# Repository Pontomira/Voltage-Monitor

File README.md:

# Voltage-Monitor
I'm trying to build a voltage monitor for Li-Po batteries, in my case 6s and i used texas instruments devices to make the gauge meter, charging and discharging control

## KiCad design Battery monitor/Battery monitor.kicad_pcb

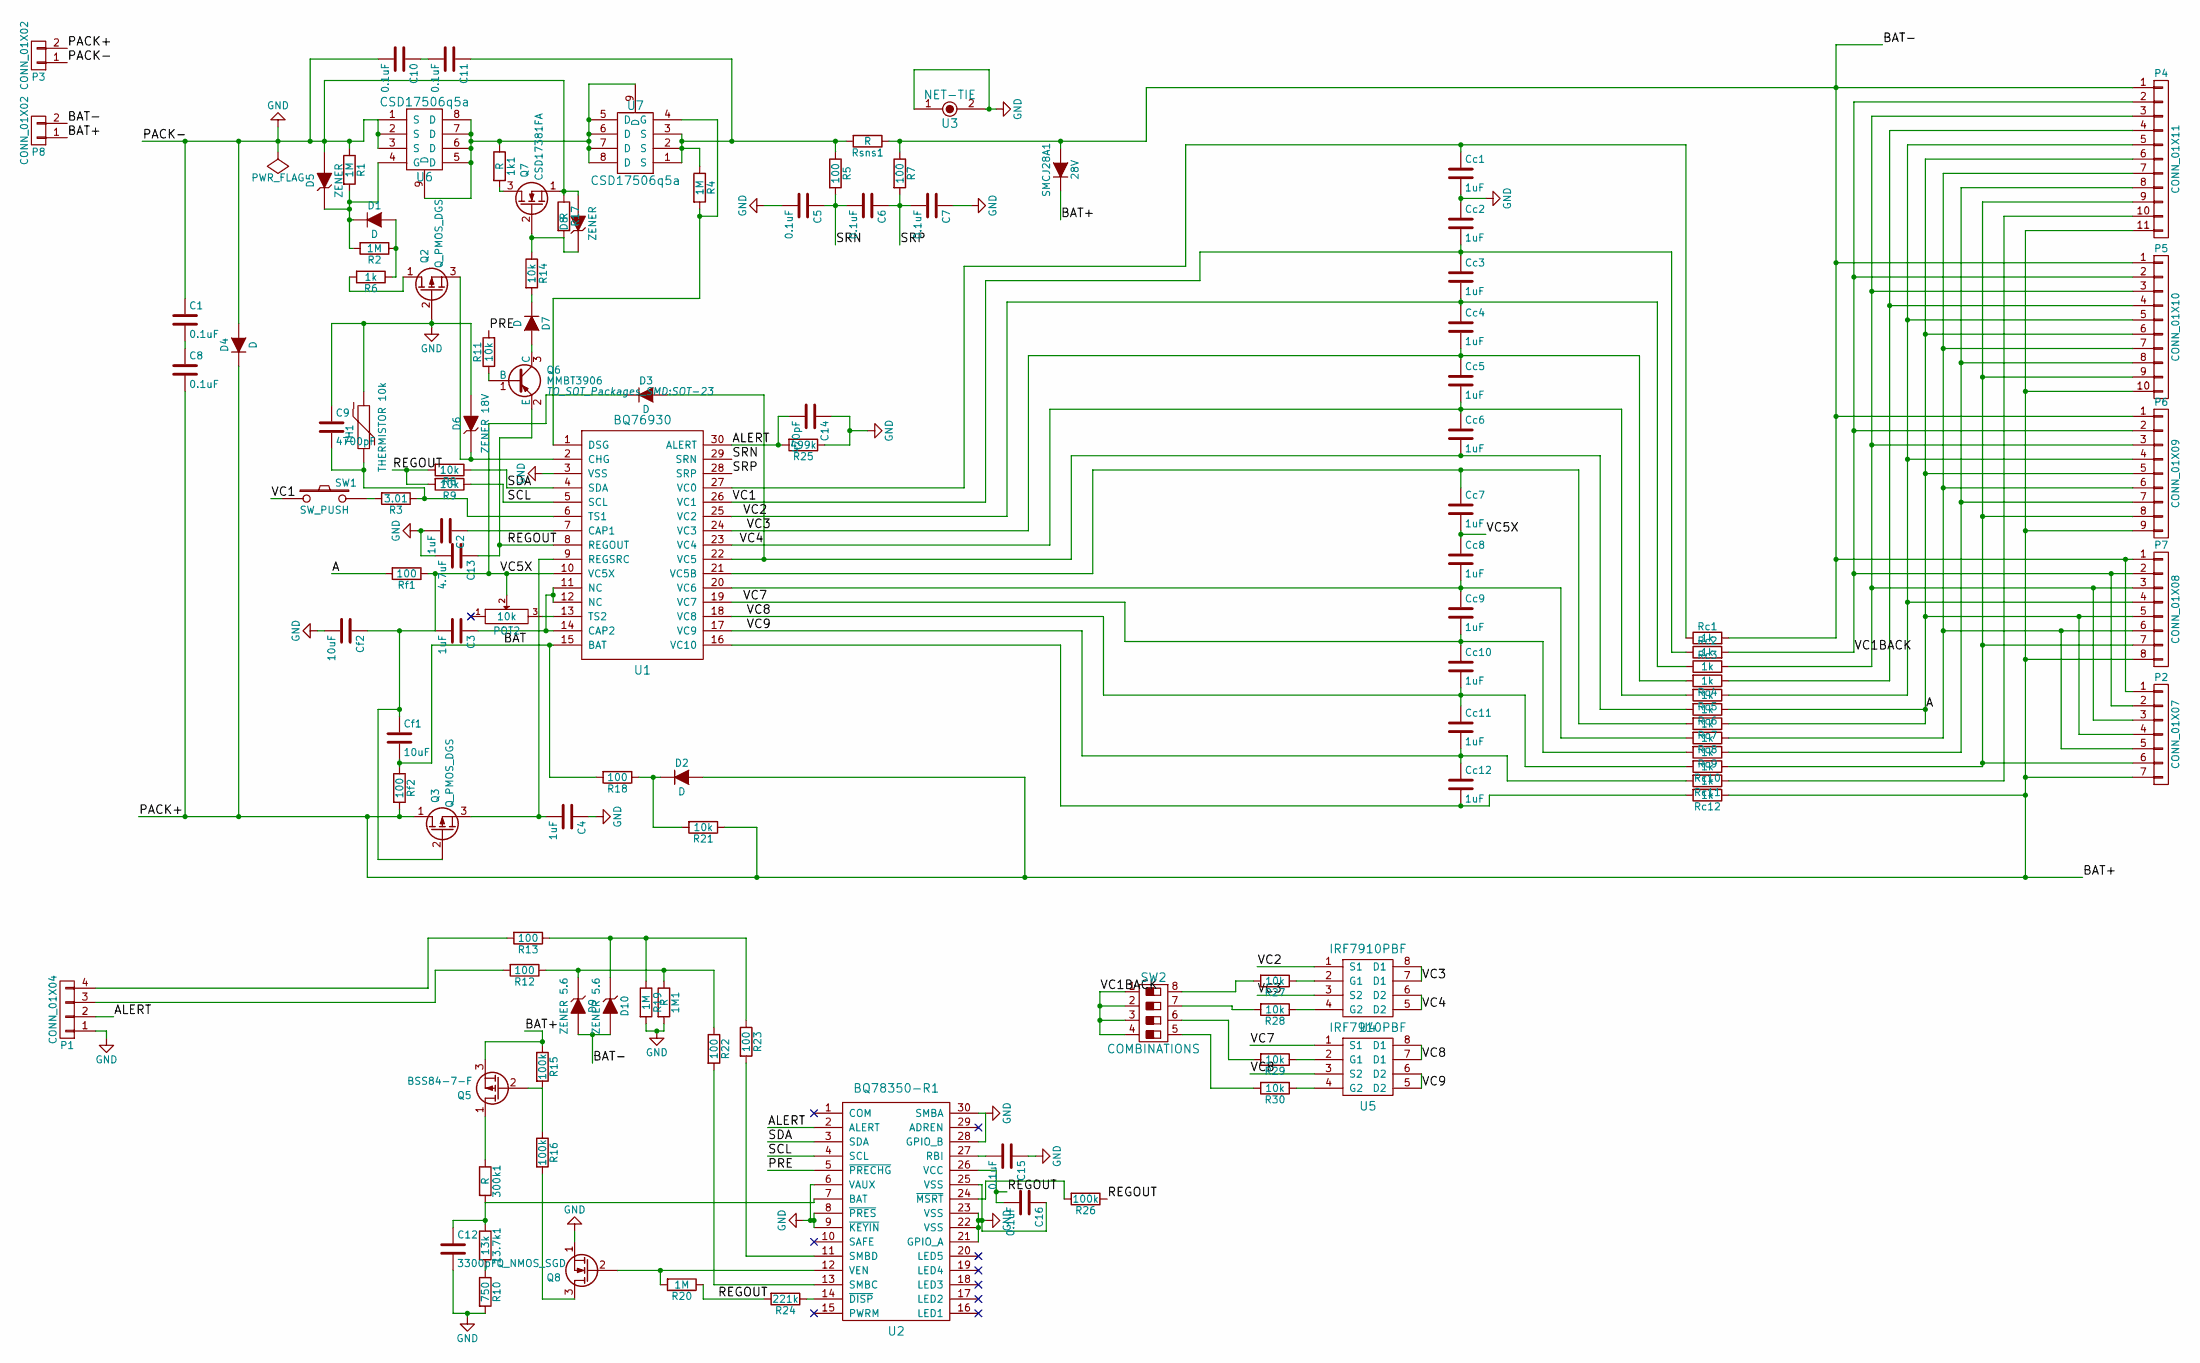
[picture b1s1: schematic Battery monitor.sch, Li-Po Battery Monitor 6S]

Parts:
1M1, 1k1, 300k1: R; R_1206_HandSoldering
13.7k1: 13k; R_1206_HandSoldering
C1: 0.1uF; R_0805_HandSoldering
C2, C3, C4: 1uF; C_0402
C5, C6, C7, C8, C10, C11, C15, C16: 0.1uF; C_0805_HandSoldering
C9: 4700pF; C_0805_HandSoldering
C12: 3300pF; C_0603_HandSoldering
C13: 4.7uF; C_0805_HandSoldering
C14: 470pF; C_0805_HandSoldering
Cc1, Cc2, Cc3, Cc4, Cc5, Cc6, Cc7, Cc8, Cc9, Cc10, Cc11, Cc12: 1uF; C_0402
Cf1, Cf2: 10uF; C_1206_HandSoldering
D1, D2, D3, D4, D7: D; DO-214AB
D5, D8: ZENER; SMA_Handsoldering
D6: ZENER 18V; SMA_Handsoldering
D9, D10: ZENER 5.6; SMA_Handsoldering
P1: CONN_01X04; Pin_Header_Straight_1x04
P2: CONN_01X07; Pin_Header_Straight_1x07
P3, P8: CONN_01X02; AK300-2
P4: CONN_01X11; Pin_Header_Straight_1x11
P5: CONN_01X10; Pin_Header_Straight_1x10
P6: CONN_01X09; Pin_Header_Straight_1x09
P7: CONN_01X08; Pin_Header_Straight_1x08
POT2: 10k; 3314-4mmsquaretrimpot
Q2, Q3: Q_PMOS_DGS; CSD17381F4T
Q5: BSS84-7-F; SOT-23
Q6: MMBT3906; SOT-23
Q7: CSD17381FA; CSD17381F4T
Q8: Q_NMOS_SGD; CSD17381F4T
R1, R2, R4, R19, R20: 1M; R_1206_HandSoldering
R3: 3.01; R_1206_HandSoldering
R5, R7, R12, R13, R18, R22, R23: 100; R_1206_HandSoldering
R6: 1k; R_1206_HandSoldering
R8, R9, R11, R14, R21, R27, R28, R29, R30: 10k; R_1206_HandSoldering
R10: 750; R_1206_HandSoldering
R15, R16, R26: 100k; R_1206_HandSoldering
R17: R; R_1206_HandSoldering
R24: 221k; R_1206_HandSoldering
R25: 499k; R_1206_HandSoldering
Rc1, Rc2, Rc3, Rc4, Rc5, Rc6, Rc7, Rc8, Rc9, Rc10, Rc11, Rc12: 1k; R_1206_HandSoldering
Rf1, Rf2: 100; R_1206_HandSoldering
Rsns1: R; 7146_SMD_POWER_RESISTOR
SMCJ28A1: 28V; SMC_Handsoldering
SW1: SW_PUSH; SW_PUSH_SMALL
SW2: COMBINATIONS; DIPS-DS04
TH1: THERMISTOR 10k; Pin_Header_Straight_1x02
U1: BQ76930; TSSOP30-7.8mmx4.4mm
U2: BQ78350-R1; TSSOP30-7.8mmx4.4mm
U3: NET-TIE
U4, U5: IRF7910PBF; SOIC-8_3.9x4.9mm_Pitch1.27mm
U6, U7: CSD17506q5a; CSD1756

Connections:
/A: P2.4, P4.6, P5.6, P6.5, P7.5, Rc6.1, Rc7.1, Rf1.2
/ALERT: C14.2, P1.2, R25.2, U1.30 (ALERT), U2.2 (ALERT)
/BAT: Cf1.2, R18.2, Rf2.1, U1.15 (BAT)
/BAT+: C8.2, D2.2 (A), D4.1 (K), P2.7, P3.2, P4.11, P5.10, P6.9, P7.8, P8.1, Q3.1 (D), Q5.3 (S), R15.1, R21.1, Rc12.1, Rf2.2, SMCJ28A1.1 (K)
/BAT-: D9.2 (A), D10.2 (A), P2.1, P4.1, P5.1, P6.1, P7.1, P8.2, R7.1, Rc1.2, Rsns1.1, SMCJ28A1.2 (A)
/PRE: R11.2, U2.5 (~PRECHG)
/REGOUT: C13.1, C16.2, Q6.2 (E), R8.2, R9.2, R20.1, R24.2, R26.1, U1.8 (REGOUT), U2.26 (VCC)
/SCL: R9.1, U1.5 (SCL), U2.4 (SCL)
/SDA: R8.1, U1.4 (SDA), U2.3 (SDA)
/SRN: C5.1, C6.2, R5.2, U1.29 (SRN)
/SRP: C6.1, C7.2, R7.2, U1.28 (SRP)
/VC1: Cc2.2, Cc3.1, Rc2.1, SW1.1, U1.26 (VC1)
/VC1BACK: P2.2, P4.2, P5.2, P6.2, P7.2, Rc2.2, SW2.1, SW2.2, SW2.3, SW2.4
/VC2: Cc3.2, Cc4.1, Rc3.1, U1.25 (VC2), U4.1 (S1)
/VC3: Cc4.2, Cc5.1, Rc4.2, U1.24 (VC3), U4.3 (S2), U4.7 (D1), U4.8 (D1)
/VC4: Cc5.2, Cc6.1, Rc5.2, U1.23 (VC4), U4.5 (D2), U4.6 (D2)
/VC5X: C3.2, Cc7.2, Cc8.1, Cf1.1, Cf2.1, D3.1 (K), POT2.2, Q3.2 (G), Rf1.1, U1.10 (VC5X)
/VC7: Cc9.2, Cc10.1, Rc9.2, U1.19 (VC7), U5.1 (S1)
/VC8: Cc10.2, Cc11.1, Rc10.2, U1.18 (VC8), U5.3 (S2), U5.7 (D1), U5.8 (D1)
/VC9: Cc11.2, Cc12.1, Rc11.2, U1.17 (VC9), U5.5 (D2), U5.6 (D2)
GND: 1M1.2, C1.1, C2.2, C4.1, C5.2, C7.1, C9.1, C10.2, C12.2, C13.2, C14.1, C15.1, C16.1, Cc1.2, Cc2.1, Cf2.2, D4.2 (A), D5.2 (A), D6.2 (A), D8.2 (A), P1.1, P3.1, Q2.2 (G), Q7.1 (S), Q8.1 (S), R1.1, R10.2, R17.1, R19.2, R25.1, TH1.2, U1.3 (VSS), U2.6 (VAUX), U2.8 (~PRES), U2.9 (~KEYIN), U2.21 (GPIO_A), U2.22 (VSS), U2.23 (VSS), U2.25 (VSS), U2.28 (GPIO_B), U2.30 (SMBA), U3.1, U3.2, U6.1 (S), U6.2 (S), U6.3 (S)
unnamed: 1M1.1, D9.1 (K), R12.1, R22.1
unnamed: 1k1.1, U6.5 (D), U6.6 (D), U6.7 (D), U6.8 (D), U6.9 (D), U7.5 (D), U7.6 (D), U7.7 (D), U7.8 (D), U7.9 (D)
unnamed: 1k1.2, Q7.3 (D)
unnamed: 13.7k1.1, 300k1.2, C12.1, U2.7 (BAT)
unnamed: 13.7k1.2, R10.1
unnamed: 300k1.1, Q5.1 (D)
unnamed: C1.2, C8.1
unnamed: C2.1, U1.7 (CAP1)
unnamed: C3.1, U1.11 (NC), U1.12 (NC), U1.14 (CAP2)
unnamed: C4.2, Q3.3 (S), U1.9 (REGSRC)
unnamed: C9.2, R3.1, TH1.1, U1.6 (TS1)
unnamed: C10.1, C11.2
unnamed: C11.1, R4.1, R5.1, Rsns1.2, U7.1 (S), U7.2 (S), U7.3 (S)
unnamed: C15.2, U2.27 (RBI)
unnamed: Cc1.1, Rc1.1, U1.27 (VC0)
unnamed: Cc6.2, D3.2 (A), Rc6.2, U1.22 (VC5)
unnamed: Cc7.1, Rc7.2, U1.21 (VC5B)
unnamed: Cc8.2, Cc9.1, Rc8.2, U1.20 (VC6)
unnamed: Cc12.2, Rc12.2, U1.16 (VC10)
unnamed: D1.1 (K), D5.1 (K), R1.2, R2.2, U6.4 (G)
unnamed: D1.2 (A), R2.1, R6.1
unnamed: D2.1 (K), R18.1, R21.2
unnamed: D6.1 (K), Q2.3 (S), U1.2 (CHG)
unnamed: D7.1 (K), R14.2
unnamed: D7.2 (A), Q6.3 (C)
unnamed: D8.1 (K), Q7.2 (G), R14.1, R17.2
unnamed: D10.1 (K), R13.1, R19.1, R23.1
unnamed: P1.3, R12.2
unnamed: P1.4, R13.2
unnamed: P2.3, P4.3, P5.3, P6.3, P7.3, Rc3.2
unnamed: P2.5, P4.7, P5.7, P6.6, P7.6, Rc8.1
unnamed: P2.6, P4.9, P5.9, P6.8, P7.7, Rc10.1
unnamed: P4.4, P5.4, Rc4.1
unnamed: P4.5, P5.5, P6.4, P7.4, Rc5.1
unnamed: P4.8, P5.8, P6.7, Rc9.1
unnamed: P4.10, Rc11.1
unnamed: POT2.3, U1.13 (TS2)
unnamed: Q2.1 (D), R6.2
unnamed: Q5.2 (G), R15.2, R16.1
unnamed: Q6.1 (B), R11.1
unnamed: Q8.2 (G), R20.2, U2.12 (VEN)
unnamed: Q8.3 (D), R16.2
unnamed: R3.2, SW1.2
unnamed: R4.2, U1.1 (DSG), U7.4 (G)
unnamed: R22.2, U2.13 (SMBC)
unnamed: R23.2, U2.11 (SMBD)
unnamed: R24.1, U2.14 (~DISP)
unnamed: R26.2, U2.24 (~MSRT)
unnamed: R27.1, U4.2 (G1)
unnamed: R27.2, SW2.8
unnamed: R28.1, U4.4 (G2)
unnamed: R28.2, SW2.7
unnamed: R29.1, U5.2 (G1)
unnamed: R29.2, SW2.6
unnamed: R30.1, U5.4 (G2)
unnamed: R30.2, SW2.5

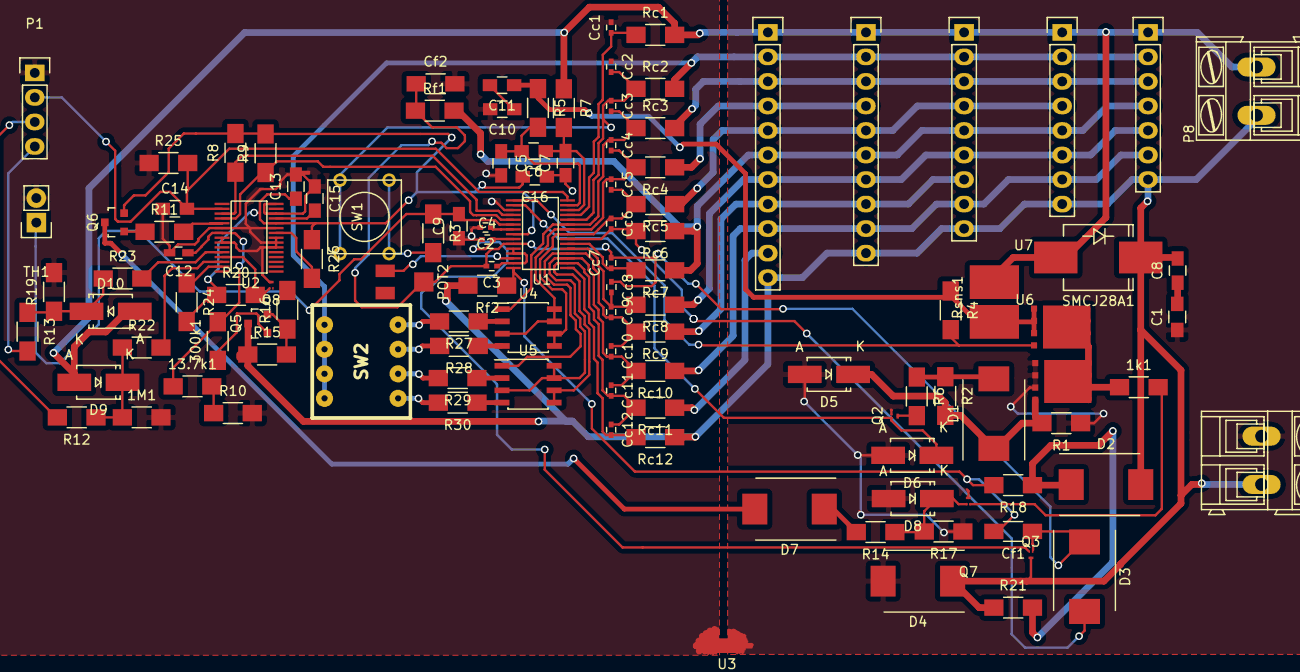
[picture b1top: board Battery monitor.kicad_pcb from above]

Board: 2 copper layers, 115 parts (0 on the bottom side), 77 nets.

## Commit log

2016-08-29 KiCad files
    I've created schematic and PCB Layout to start with (not the best) it was the first
2017-04-19 ProbotSchematic.xml
2017-04-19 Probot_Diagram.xml
